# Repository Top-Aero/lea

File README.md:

# LEA – Lanceur Expérimental ~~d'Atterrissage~~ d'Apprentissage

Projet de l'association Top Aéro. Il s'agit d'une minifusée prévue pour être lancée durant la campagne 2023 du C'Space. Le but est qu'elle atterrisse en se posant au sol debout, ogive haute et pieds déployés.

Ce dépôt contient la conception électronique de ce projet.

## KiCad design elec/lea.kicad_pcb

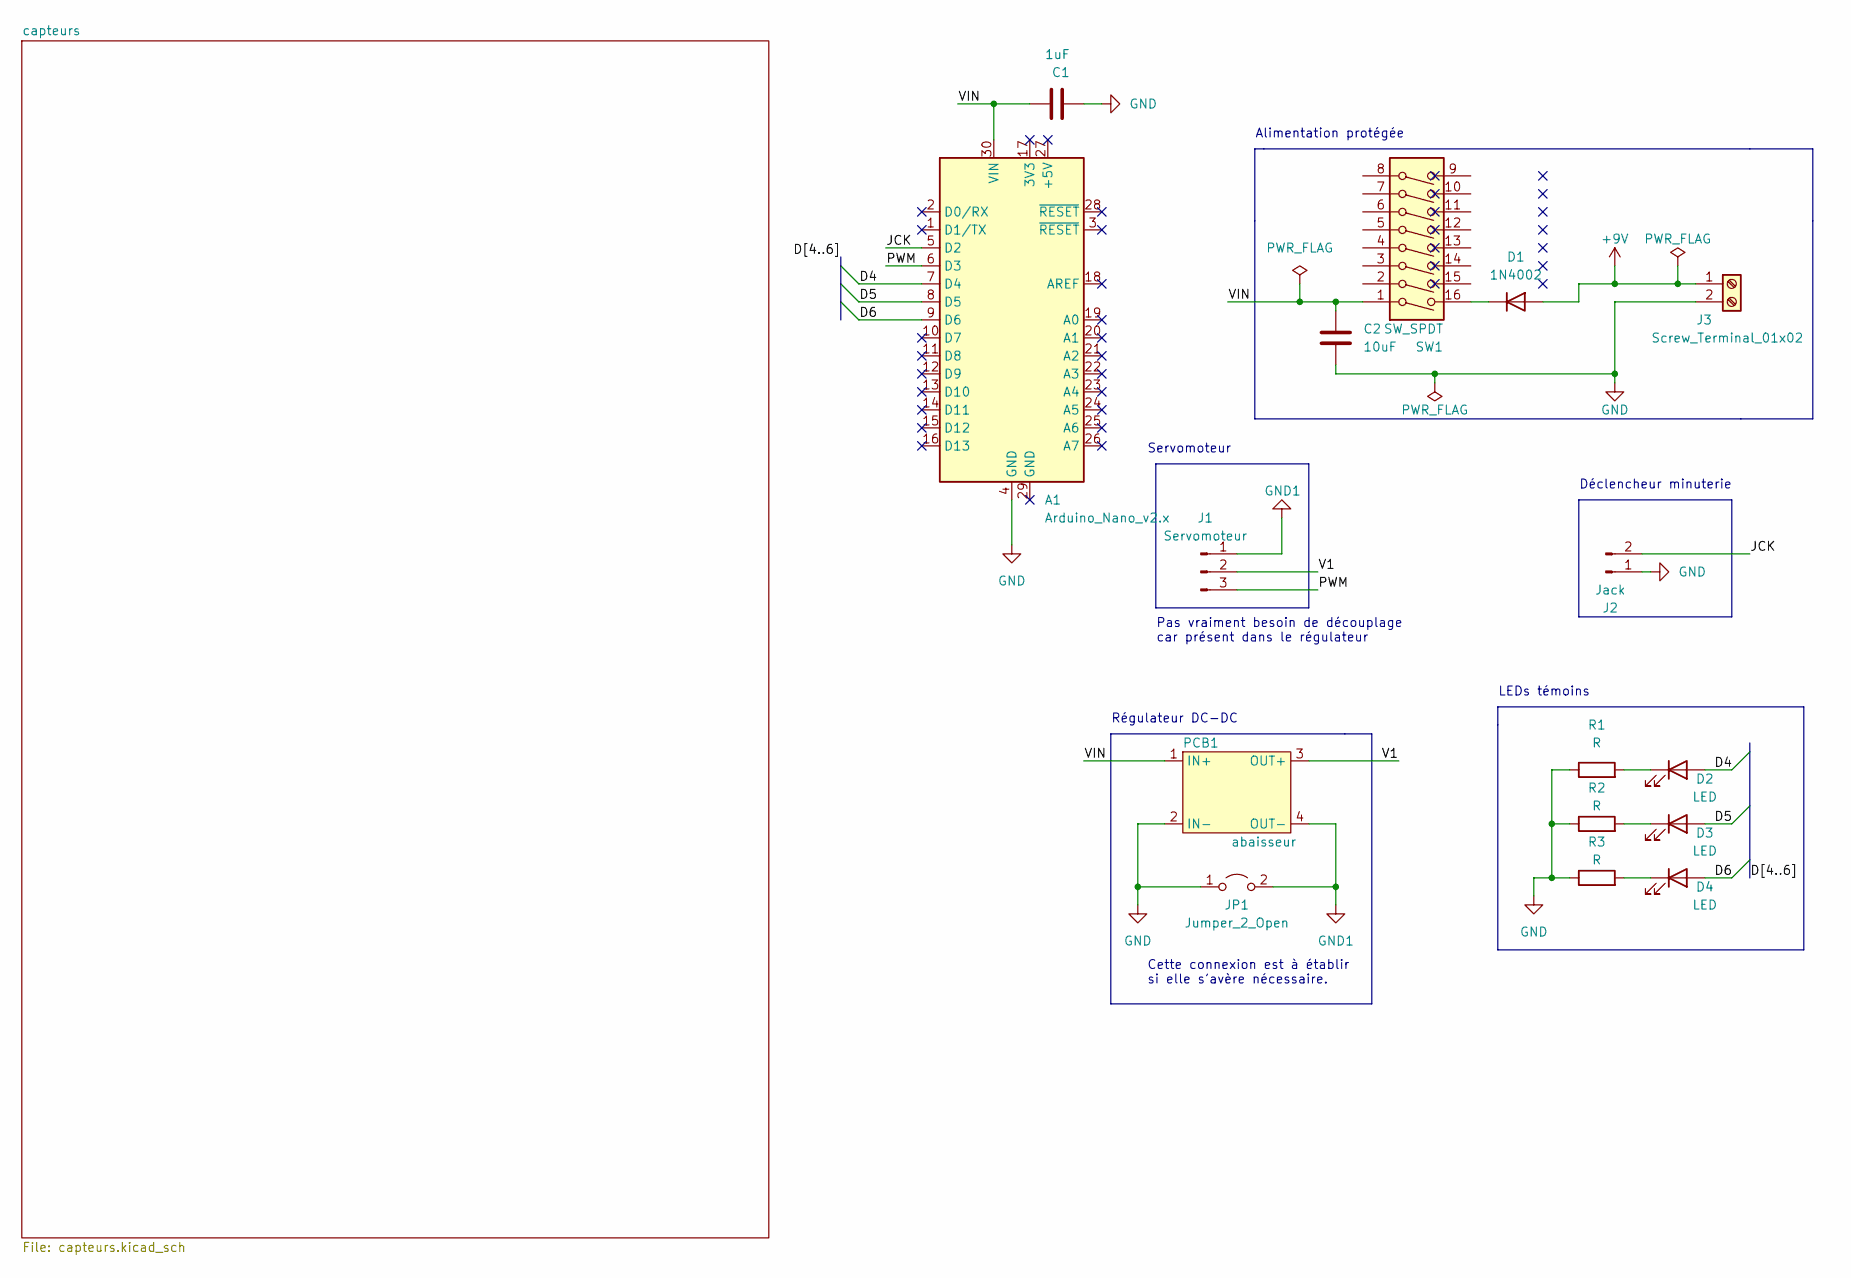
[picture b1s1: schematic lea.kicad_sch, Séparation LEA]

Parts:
A1: Arduino_Nano_v2.x; Arduino_Nano
C1: 1uF; C_Axial_L3.8mm_D2.6mm_P7.50mm_Horizontal
C2: 10uF; C_Radial_D6.3mm_H5.0mm_P2.50mm
D1: 1N4002; D_DO-41_SOD81_P10.16mm_Horizontal
D2, D3, D4: LED; LED_D5.0mm
J1: Servomoteur; JST_XH_B3B-XH-A_1x03_P2.50mm_Vertical
J2: Jack; JST_XH_B2B-XH-A_1x02_P2.50mm_Vertical
J3: Screw_Terminal_01x02; TerminalBlock_Phoenix_MKDS-1,5-2-5.08_1x02_P5.08mm_Horizont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
JP1: Jumper_2_Open; PinSocket_1x02_P2.54mm_Vertical
PCB1: abaisseur; abaisseur_TOP-AERO
R1, R2, R3: R; R_Axial_DIN0309_L9.0mm_D3.2mm_P12.70mm_Horizontal
SW1: SW_SPDT; SW_DIP_SPSTx08_Slide_9.78x22.5mm_W7.62mm_P2.54mm

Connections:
+9V: D1.2 (A), J3.1
/D4: A1.7 (D4), D2.2 (A)
/D5: A1.8 (D5), D3.2 (A)
/D6: A1.9 (D6), D4.2 (A)
/JCK: A1.5 (D2), J2.2
/PWM: A1.6 (D3), J1.3
/V1: J1.2, PCB1.3 (OUT+)
/VIN: A1.30 (VIN), C1.1, C2.2, PCB1.1 (IN+), SW1.1
GND: A1.4 (GND), C1.2, C2.1, J2.1, J3.2, JP1.1 (A), PCB1.2 (IN-), R1.1, R2.1, R3.1
GND1: J1.1, JP1.2 (B), PCB1.4 (OUT-)
unnamed: D2.1 (K), R1.2
unnamed: D3.1 (K), R2.2
unnamed: D4.1 (K), R3.2
unnamed: D1.1 (K), SW1.16

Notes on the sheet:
Pas vraiment besoin de découplage car présent dans le régulateur
Déclencheur minuterie
Servomoteur
Cette connexion est à établir si elle s'avère nécessaire.
Alimentation protégée
LEDs témoins
Régulateur DC-DC

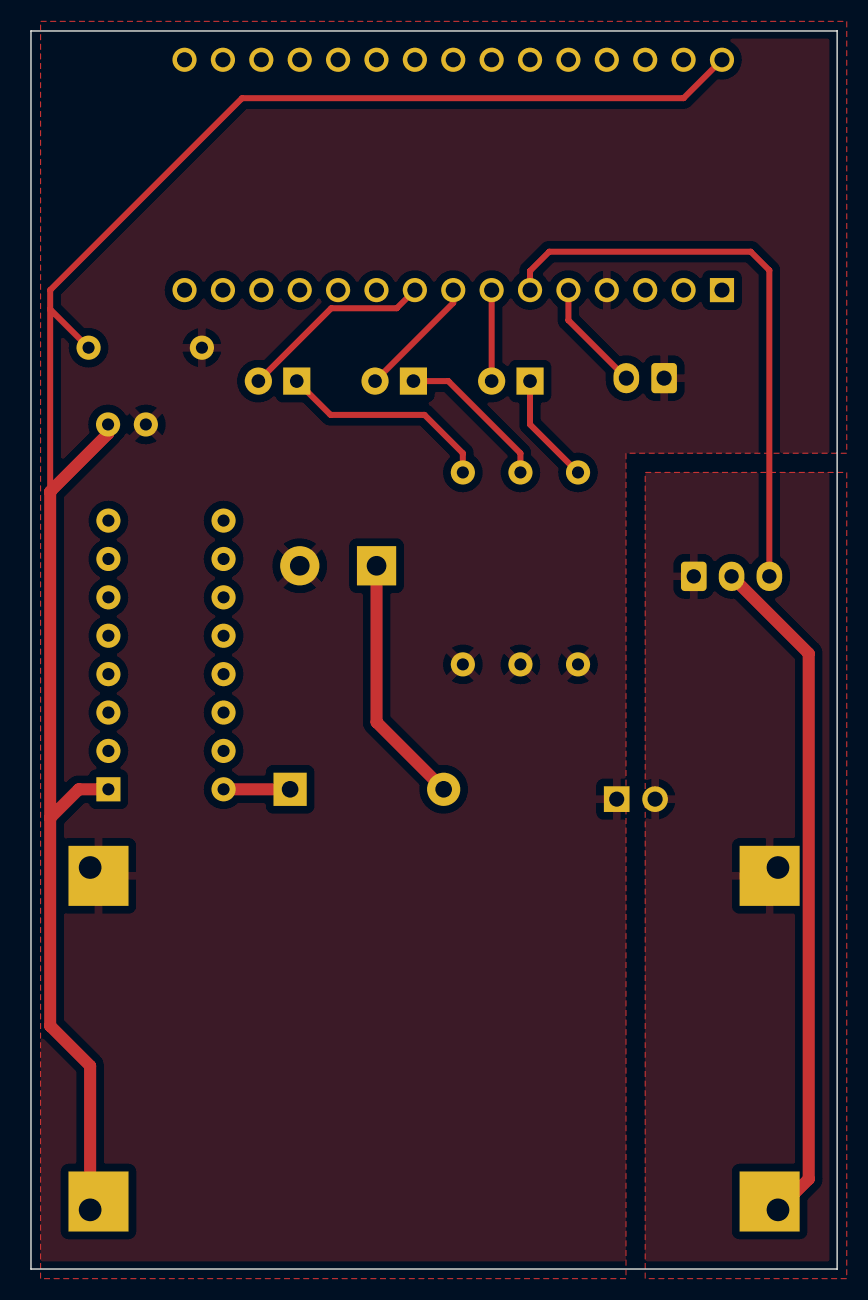
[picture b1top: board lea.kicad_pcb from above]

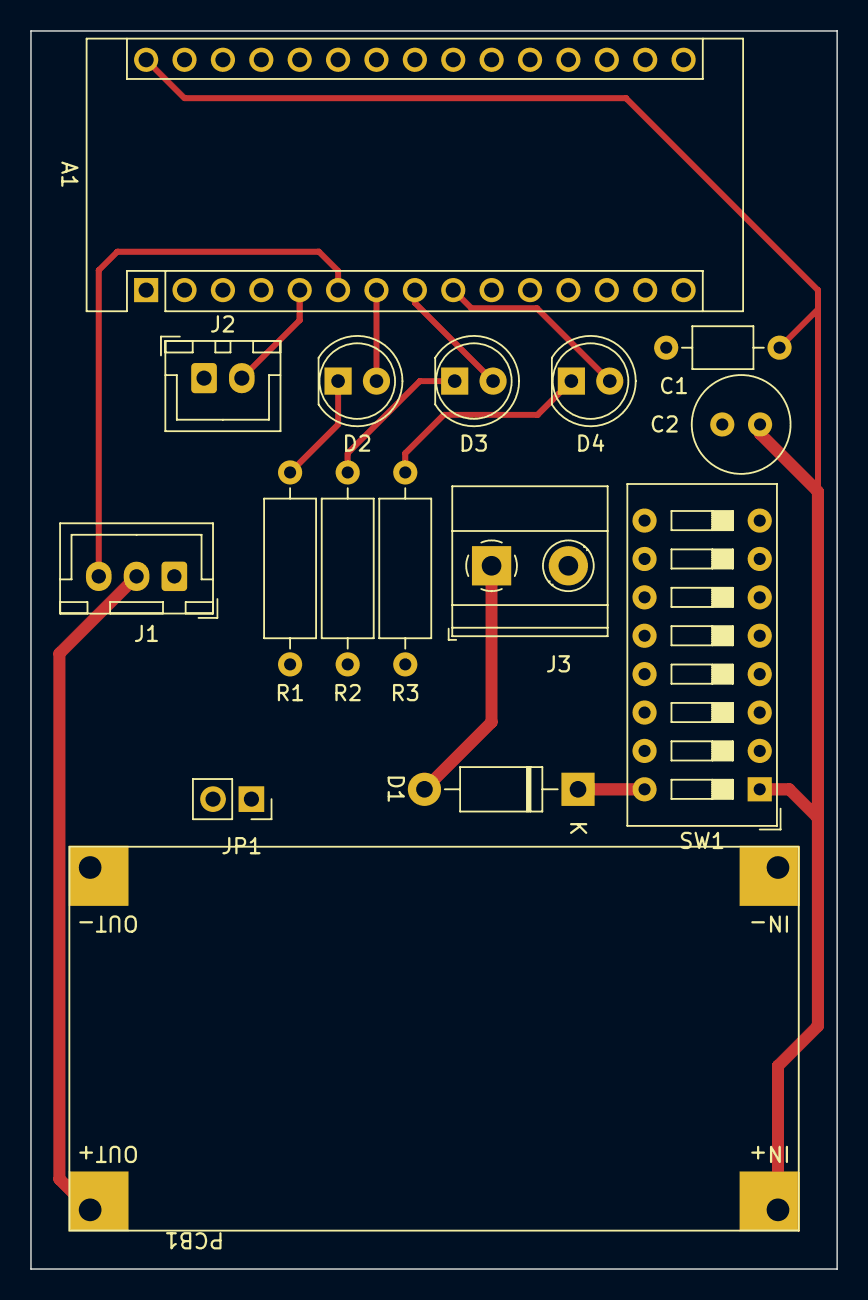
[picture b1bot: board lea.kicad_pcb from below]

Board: 2 copper layers, 53.3 x 81.9 mm, 16 parts (16 on the bottom side), 14 nets.

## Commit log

2023-01-07 màj gitignore et readme
2023-01-07 correction du gitignore
2023-01-07 Début de conception basée sur Arduino Nano
    Éléments remarquables :
    - diode de protection dans bloc d'alimentation
    - servomoteur découplé dans bloc actionneur
    - Jack simple dont il faut déterminer le besoin ou non d'une résistance
    externe pull-up ou pull-down
2023-04-11 avancement des schémas et pcb
2023-04-29 commit avant changement de branche
2023-05-25 Refonte complète du circuit
    - réagencement des composants sur le schéma
    - pcb désormais rectangulaire
    - ajout du régulateur de tension et de son empreinte
    - masses séparées avec possibilité de pont
2023-05-25 version du pcb usinable au fablab
2023-05-25 léger changement dans la direction du projet
2023-06-04 switch dorénavant au format dip et nouveeau schéma pour circuit bonus
